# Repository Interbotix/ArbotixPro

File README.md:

# ArbotixPro
Eagle design files for Arbotix-Pro Robocontroller & source for CM730-compatible & ROS firmware versions.

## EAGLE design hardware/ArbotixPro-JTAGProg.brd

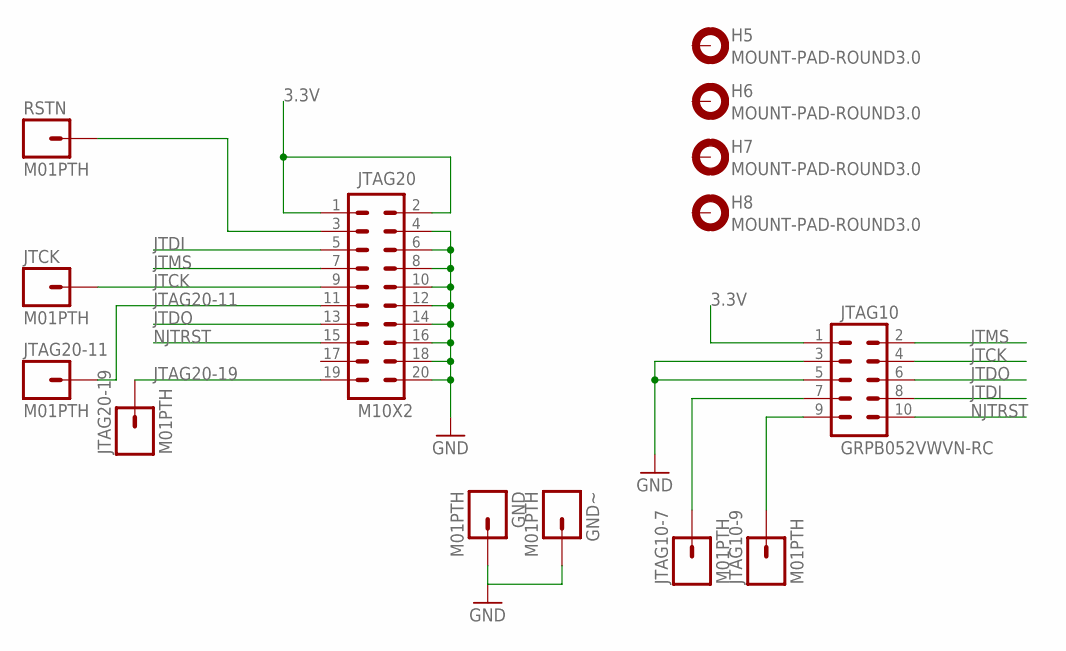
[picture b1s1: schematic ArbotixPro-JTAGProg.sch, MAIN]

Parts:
GND: M01PTH; 1X01
GND~: M01PTH; 1X01
H5, H6, H7, H8: MOUNT-PAD-ROUND3.0; 3,0-PAD
JTAG10: GRPB052VWVN-RC; 2X5_PTH_SILK_.05
JTAG10-7, JTAG10-9, JTAG20-11, JTAG20-19: M01PTH; 1X01
JTAG20: M10X2; 2X10
JTCK: M01PTH; 1X01
RSTN: M01PTH; 1X01

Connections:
3.3V: JTAG10.1, JTAG20.1, JTAG20.2
GND: GND.1, GND~.1, JTAG10.3, JTAG10.5, JTAG20.4, JTAG20.6, JTAG20.8, JTAG20.10, JTAG20.12, JTAG20.14, JTAG20.16, JTAG20.18, JTAG20.20
JTAG20-11: JTAG20.11, JTAG20-11.1
JTAG20-19: JTAG20.19, JTAG20-19.1
JTCK: JTAG10.4, JTAG20.9, JTCK.1
JTDI: JTAG10.8, JTAG20.5
JTDO: JTAG10.6, JTAG20.13
JTMS: JTAG10.2, JTAG20.7
unnamed: JTAG10.7, JTAG10-7.1
unnamed: JTAG10.9, JTAG10-9.1
NJTRST: JTAG10.10, JTAG20.15
RSTN: JTAG20.3, RSTN.1

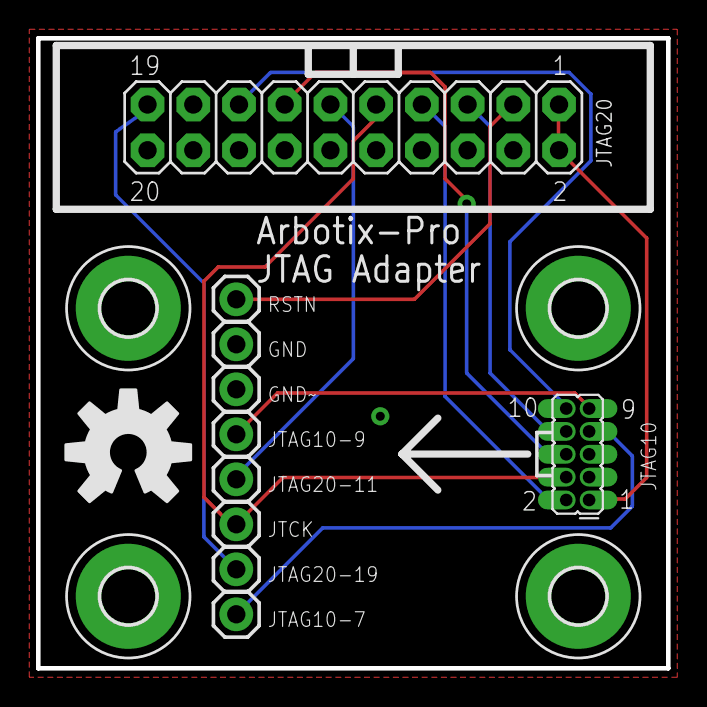
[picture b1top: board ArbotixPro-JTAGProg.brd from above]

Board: 2 copper layers, 35.0 x 35.0 mm, 15 parts (0 on the bottom side), 12 nets.

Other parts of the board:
U$1: OSHW-LOGO-L

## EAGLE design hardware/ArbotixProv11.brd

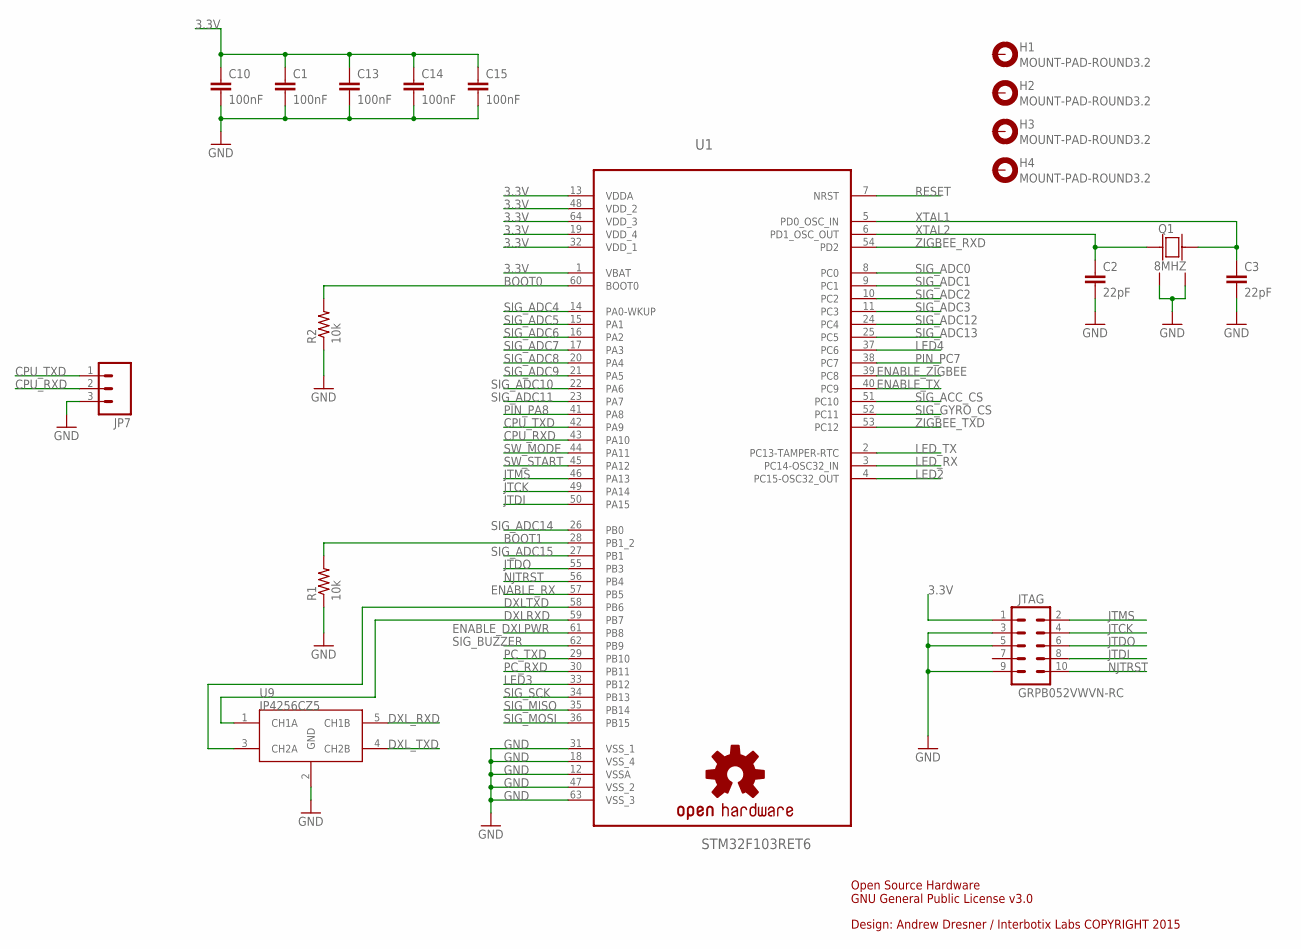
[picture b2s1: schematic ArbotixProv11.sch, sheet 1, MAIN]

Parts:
C1, C10, C13, C14, C15: 100nF; 0603-CAP
C2, C3: 22pF; 0603-CAP
H1, H2, H3, H4: MOUNT-PAD-ROUND3.2; 3,2-PAD
JP7: M03PTH; 1X03
JTAG: GRPB052VWVN-RC; 2X5_PTH_SILK_.05
LOGO1: OSHW-LOGOM; OSHW-LOGO-M
Q1: 8MHZ; 4LCC
R1, R2: 10k; 0603-RES
U1: STM32F103RET6; QFP50P1200X1200X160-64N
U9: IP4256CZ5; SOT665

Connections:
3.3V: C1.1, C10.1, C13.1, C14.1, C15.1, JTAG.1, U1.1 (VBAT), U1.13 (VDDA), U1.19 (VDD_4), U1.32 (VDD_1), U1.48 (VDD_2), U1.64 (VDD_3); also elsewhere on the board
BOOT0: R2.2, U1.60 (BOOT0)
BOOT1: R1.2, U1.28 (PB1_2)
CPU_RXD: JP7.2, U1.43 (PA10)
CPU_TXD: JP7.1, U1.42 (PA9)
DXLRXD: U1.59 (PB7), U9.1 (CH1A)
DXLTXD: U1.58 (PB6), U9.3 (CH2A)
DXL_RXD: U9.5 (CH1B); also elsewhere on the board
DXL_TXD: U9.4 (CH2B); also elsewhere on the board
ENABLE_DXLPWR: U1.61 (PB8); also elsewhere on the board
ENABLE_RX: U1.57 (PB5); also elsewhere on the board
ENABLE_TX: U1.40 (PC9); also elsewhere on the board
ENABLE_ZIGBEE: U1.39 (PC8); also elsewhere on the board
GND: C1.2, C2.2, C3.2, C10.2, C13.2, C14.2, C15.2, JP7.3, JTAG.3, JTAG.5, JTAG.9, Q1.2, Q1.4, R1.1, R2.1, U1.12 (VSSA), U1.18 (VSS_4), U1.31 (VSS_1), U1.47 (VSS_2), U1.63 (VSS_3), U9.2 (GND); also elsewhere on the board
JTCK: JTAG.4, U1.49 (PA14)
JTDI: JTAG.8, U1.50 (PA15)
JTDO: JTAG.6, U1.55 (PB3)
JTMS: JTAG.2, U1.46 (PA13)
LED2: U1.4 (PC15-OSC32_OUT); also elsewhere on the board
LED3: U1.33 (PB12); also elsewhere on the board
LED4: U1.37 (PC6); also elsewhere on the board
LED_RX: U1.3 (PC14-OSC32_IN); also elsewhere on the board
LED_TX: U1.2 (PC13-TAMPER-RTC); also elsewhere on the board
NJTRST: JTAG.10, U1.56 (PB4)
PC_RXD: U1.30 (PB11); also elsewhere on the board
PC_TXD: U1.29 (PB10); also elsewhere on the board
PIN_PA8: U1.41 (PA8); also elsewhere on the board
PIN_PC7: U1.38 (PC7)
RESET: U1.7 (NRST); also elsewhere on the board
SIG_ACC_CS: U1.51 (PC10); also elsewhere on the board
SIG_ADC0: U1.8 (PC0); also elsewhere on the board
SIG_ADC1: U1.9 (PC1); also elsewhere on the board
SIG_ADC2: U1.10 (PC2); also elsewhere on the board
SIG_ADC3: U1.11 (PC3); also elsewhere on the board
SIG_ADC4: U1.14 (PA0-WKUP); also elsewhere on the board
SIG_ADC5: U1.15 (PA1); also elsewhere on the board
SIG_ADC6: U1.16 (PA2); also elsewhere on the board
SIG_ADC7: U1.17 (PA3); also elsewhere on the board
SIG_ADC8: U1.20 (PA4); also elsewhere on the board
SIG_ADC9: U1.21 (PA5); also elsewhere on the board
SIG_ADC10: U1.22 (PA6); also elsewhere on the board
SIG_ADC11: U1.23 (PA7); also elsewhere on the board
SIG_ADC12: U1.24 (PC4); also elsewhere on the board
SIG_ADC13: U1.25 (PC5); also elsewhere on the board
SIG_ADC14: U1.26 (PB0); also elsewhere on the board
SIG_ADC15: U1.27 (PB1); also elsewhere on the board
SIG_BUZZER: U1.62 (PB9); also elsewhere on the board
SIG_GYRO_CS: U1.52 (PC11); also elsewhere on the board
SIG_MISO: U1.35 (PB14); also elsewhere on the board
SIG_MOSI: U1.36 (PB15); also elsewhere on the board
SIG_SCK: U1.34 (PB13); also elsewhere on the board
SW_MODE: U1.44 (PA11); also elsewhere on the board
SW_START: U1.45 (PA12); also elsewhere on the board
XTAL1: C3.1, Q1.3, U1.5 (PD0_OSC_IN)
XTAL2: C2.1, Q1.1, U1.6 (PD1_OSC_OUT)
ZIGBEE_RXD: U1.54 (PD2); also elsewhere on the board
ZIGBEE_TXD: U1.53 (PC12); also elsewhere on the board

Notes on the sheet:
Design: Andrew Dresner / Interbotix Labs COPYRIGHT 2015
Open Source Hardware GNU General Public License v3.0

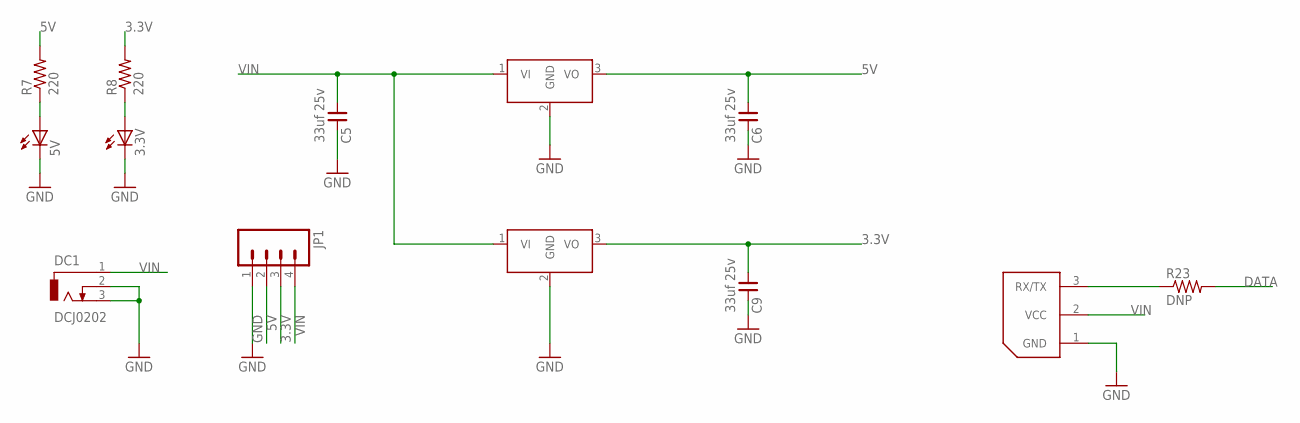
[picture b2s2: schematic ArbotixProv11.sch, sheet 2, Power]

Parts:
3.3V, 5V: LEDCHIPLED_0603; CHIPLED_0603
3V3REG: DCDC_OKI-78SR-3.3; OKI-78SRH
5VREG: DCDC_OKI-78SR-5; OKI-78SRH
C5, C6, C9: 33uf 25v; SV-C
CPU-POWER: WM18887-ND; BIOLOID
DC1: DCJ0202
JP1: M04PTH; 1X04
R7, R8: 220; 0603-RES
R23: DNP; 0603-RES

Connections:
3.3V: 3V3REG.3 (VO), C9.+ (1), JP1.3, R8.2; also elsewhere on the board
5V: 5VREG.3 (VO), C6.+ (1), JP1.2, R7.2; also elsewhere on the board
DATA: R23.2; also elsewhere on the board
GND: 3.3V.C, 3V3REG.2 (GND), 5V.C, 5VREG.2 (GND), C5.- (2), C6.- (2), C9.- (2), CPU-POWER.1 (GND), DC1.2, DC1.3, JP1.1; also elsewhere on the board
unnamed: CPU-POWER.3 (RX/TX), R23.1
unnamed: 5V.A, R7.1
unnamed: 3.3V.A, R8.1
VIN: 3V3REG.1 (VI), 5VREG.1 (VI), C5.+ (1), CPU-POWER.2 (VCC), DC1.1, JP1.4; also elsewhere on the board

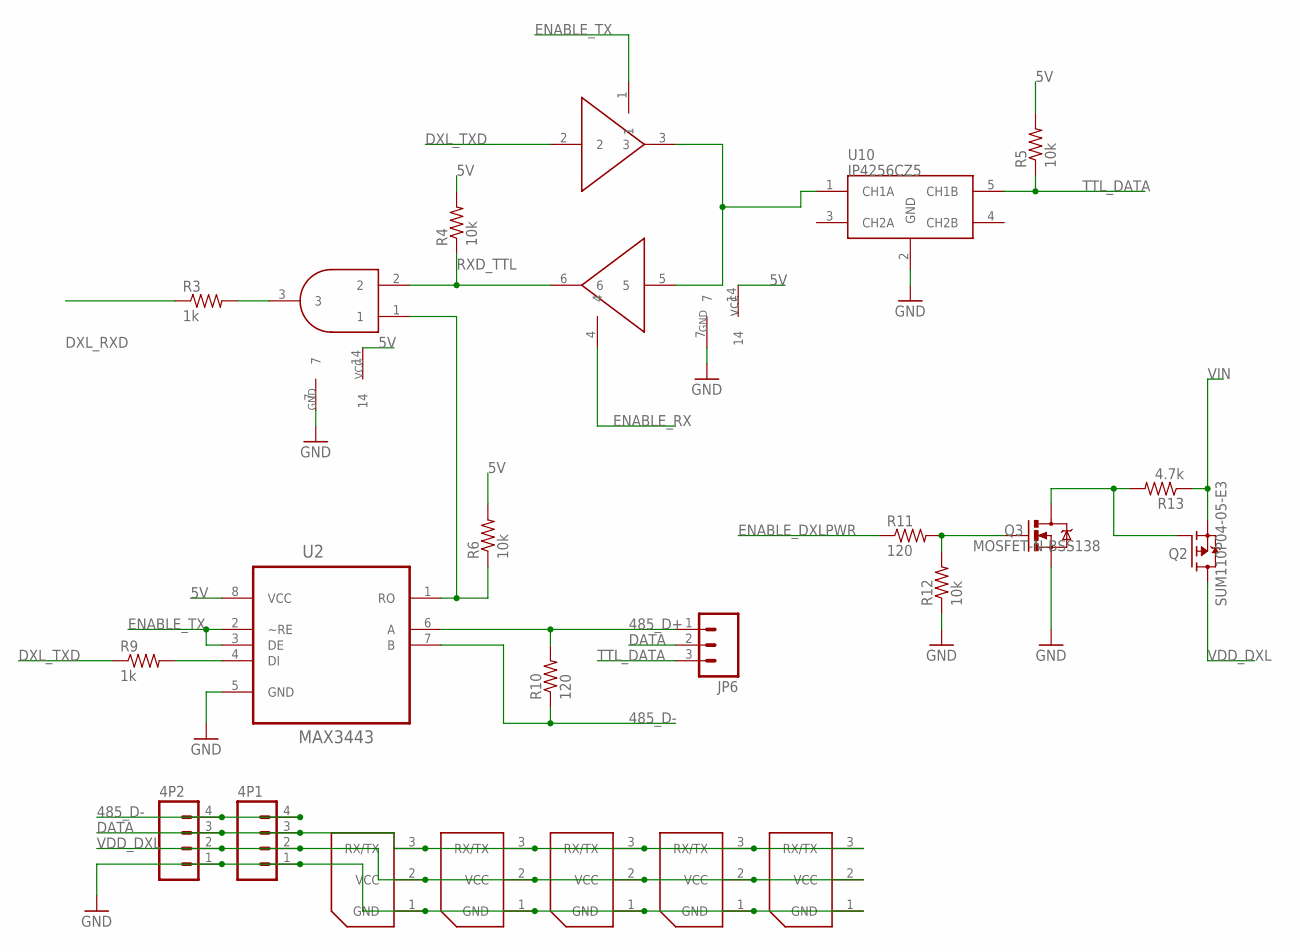
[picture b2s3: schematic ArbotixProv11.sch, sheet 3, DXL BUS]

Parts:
3P1, 3P2, 3P3, 3P4, 3P5: WM18887-ND; BIOLOID
4P1, 4P2: M04PTH; 1X04
JP6: M03PTH; 1X03
Q2: SUM110P04-05-E3; TO263
Q3: MOSFET-N-BSS138; SOT23
R3, R9: 1k; 0603-RES
R4, R5, R6, R12: 10k; 0603-RES
R10, R11: 120; 0603-RES
R13: 4.7k; 0603-RES
U2: MAX3443; SOIC127P600X175-8N
U6: 74HC08D,653; 14-SOIC
U7: 74HC126D,653; 14-SOIC
U10: IP4256CZ5; SOT665

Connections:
5V: R4.2, R5.2, R6.2, U2.8 (VCC), U6.14, U7.14; also elsewhere on the board
485_D+: JP6.1, R10.2, U2.6 (A)
485_D-: 4P1.4, 4P2.4, R10.1, U2.7 (B)
DATA: 3P1.3 (RX/TX), 3P2.3 (RX/TX), 3P3.3 (RX/TX), 3P4.3 (RX/TX), 3P5.3 (RX/TX), 4P1.3, 4P2.3, JP6.2; also elsewhere on the board
DXL_RXD: R3.1; also elsewhere on the board
DXL_TXD: R9.1, U7.2; also elsewhere on the board
ENABLE_DXLPWR: R11.1; also elsewhere on the board
ENABLE_RX: U7.4; also elsewhere on the board
ENABLE_TX: U2.2 (~RE), U2.3 (DE), U7.1; also elsewhere on the board
GND: 3P1.1 (GND), 3P2.1 (GND), 3P3.1 (GND), 3P4.1 (GND), 3P5.1 (GND), 4P1.1, 4P2.1, Q3.2 (S), R12.1, U2.5 (GND), U6.7, U7.7, U10.2 (GND); also elsewhere on the board
unnamed: Q3.1 (G), R11.2, R12.2
unnamed: R3.2, U6.3
unnamed: R9.2, U2.4 (DI)
unnamed: R6.1, U2.1 (RO), U6.1
unnamed: Q2.1 (G), Q3.3 (D), R13.2
unnamed: U7.3, U7.5, U10.1 (CH1A)
RXD_TTL: R4.1, U6.2, U7.6
TTL_DATA: JP6.3, R5.1, U10.5 (CH1B)
VDD_DXL: 3P1.2 (VCC), 3P2.2 (VCC), 3P3.2 (VCC), 3P4.2 (VCC), 3P5.2 (VCC), 4P1.2, 4P2.2, Q2.3 (D)
VIN: Q2.2 (S), R13.1; also elsewhere on the board

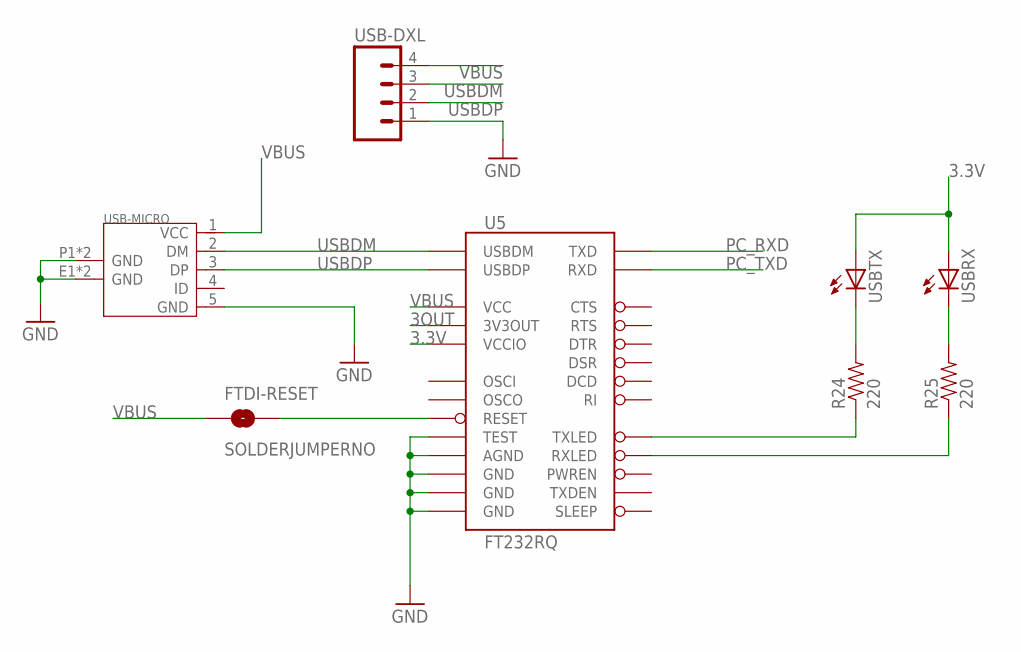
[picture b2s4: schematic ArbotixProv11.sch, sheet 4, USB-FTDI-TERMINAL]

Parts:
FTDI-RESET: SOLDERJUMPERNO; SJ_2S-NO
R24, R25: 220; 0603-RES
U5: FT232RQ; QFN-32
USB-DXL: M04PTH; 1X04
USB-MICRO: MICRO-USB-5P-340015001; B-SMD-5P
USBRX: LEDCHIPLED_0603; CHIPLED_0603
USBTX: LEDCHIPLED_0603; CHIPLED_0603

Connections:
3.3V: U5.1 (VCCIO), USBRX.A, USBTX.A; also elsewhere on the board
3OUT: U5.16 (3V3OUT)
GND: U5.4 (GND), U5.17 (GND), U5.20 (GND), U5.24 (AGND), U5.26 (TEST), USB-DXL.1, USB-MICRO.5 (GND), USB-MICRO.E1 (GND), USB-MICRO.E2 (GND), USB-MICRO.P1 (GND), USB-MICRO.P2 (GND); also elsewhere on the board
unnamed: FTDI-RESET.2, U5.18 (RESET)
unnamed: R24.2, USBTX.C
unnamed: R25.2, USBRX.C
unnamed: R24.1, U5.22 (TXLED)
unnamed: R25.1, U5.21 (RXLED)
PC_RXD: U5.30 (TXD); also elsewhere on the board
PC_TXD: U5.2 (RXD); also elsewhere on the board
USBDM: U5.15 (USBDM), USB-DXL.3, USB-MICRO.2 (DM)
USBDP: U5.14 (USBDP), USB-DXL.2, USB-MICRO.3 (DP)
VBUS: FTDI-RESET.1, U5.19 (VCC), USB-DXL.4, USB-MICRO.1 (VCC)

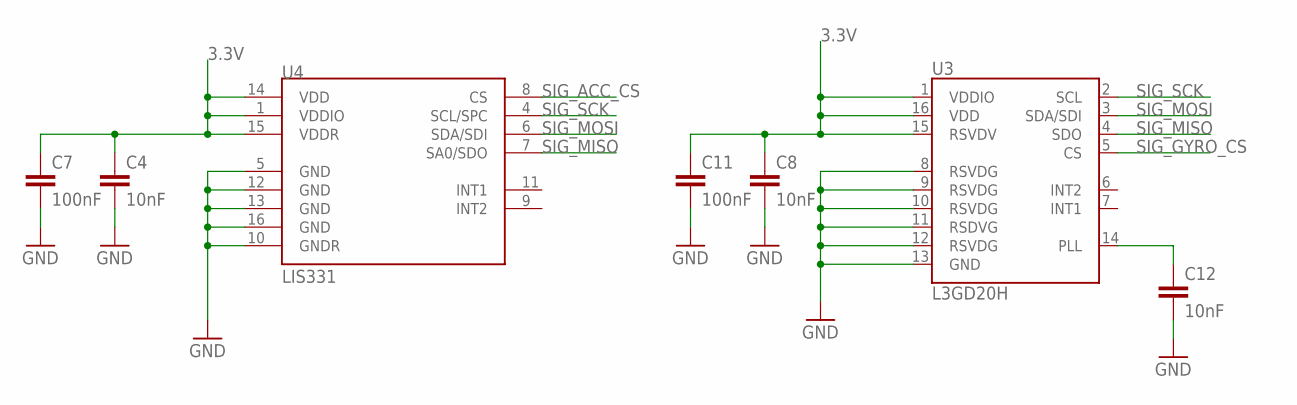
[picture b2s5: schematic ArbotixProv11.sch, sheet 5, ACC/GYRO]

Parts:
C4, C8, C12: 10nF; 0603-CAP
C7, C11: 100nF; 0603-CAP
U3: L3GD20H; LGA16-3MM
U4: LIS331; LGA16-3MM

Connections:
3.3V: C4.1, C7.1, C8.1, C11.1, U3.1 (VDDIO), U3.15 (RSVDV), U3.16 (VDD), U4.1 (VDDIO), U4.14 (VDD), U4.15 (VDDR); also elsewhere on the board
GND: C4.2, C7.2, C8.2, C11.2, C12.2, U3.8 (RSVDG), U3.9 (RSVDG), U3.10 (RSVDG), U3.11 (RSDVG), U3.12 (RSVDG), U3.13 (GND), U4.5 (GND), U4.10 (GNDR), U4.12 (GND), U4.13 (GND), U4.16 (GND); also elsewhere on the board
unnamed: C12.1, U3.14 (PLL)
SIG_ACC_CS: U4.8 (CS); also elsewhere on the board
SIG_GYRO_CS: U3.5 (CS); also elsewhere on the board
SIG_MISO: U3.4 (SDO), U4.7 (SA0/SDO); also elsewhere on the board
SIG_MOSI: U3.3 (SDA/SDI), U4.6 (SDA/SDI); also elsewhere on the board
SIG_SCK: U3.2 (SCL), U4.4 (SCL/SPC); also elsewhere on the board

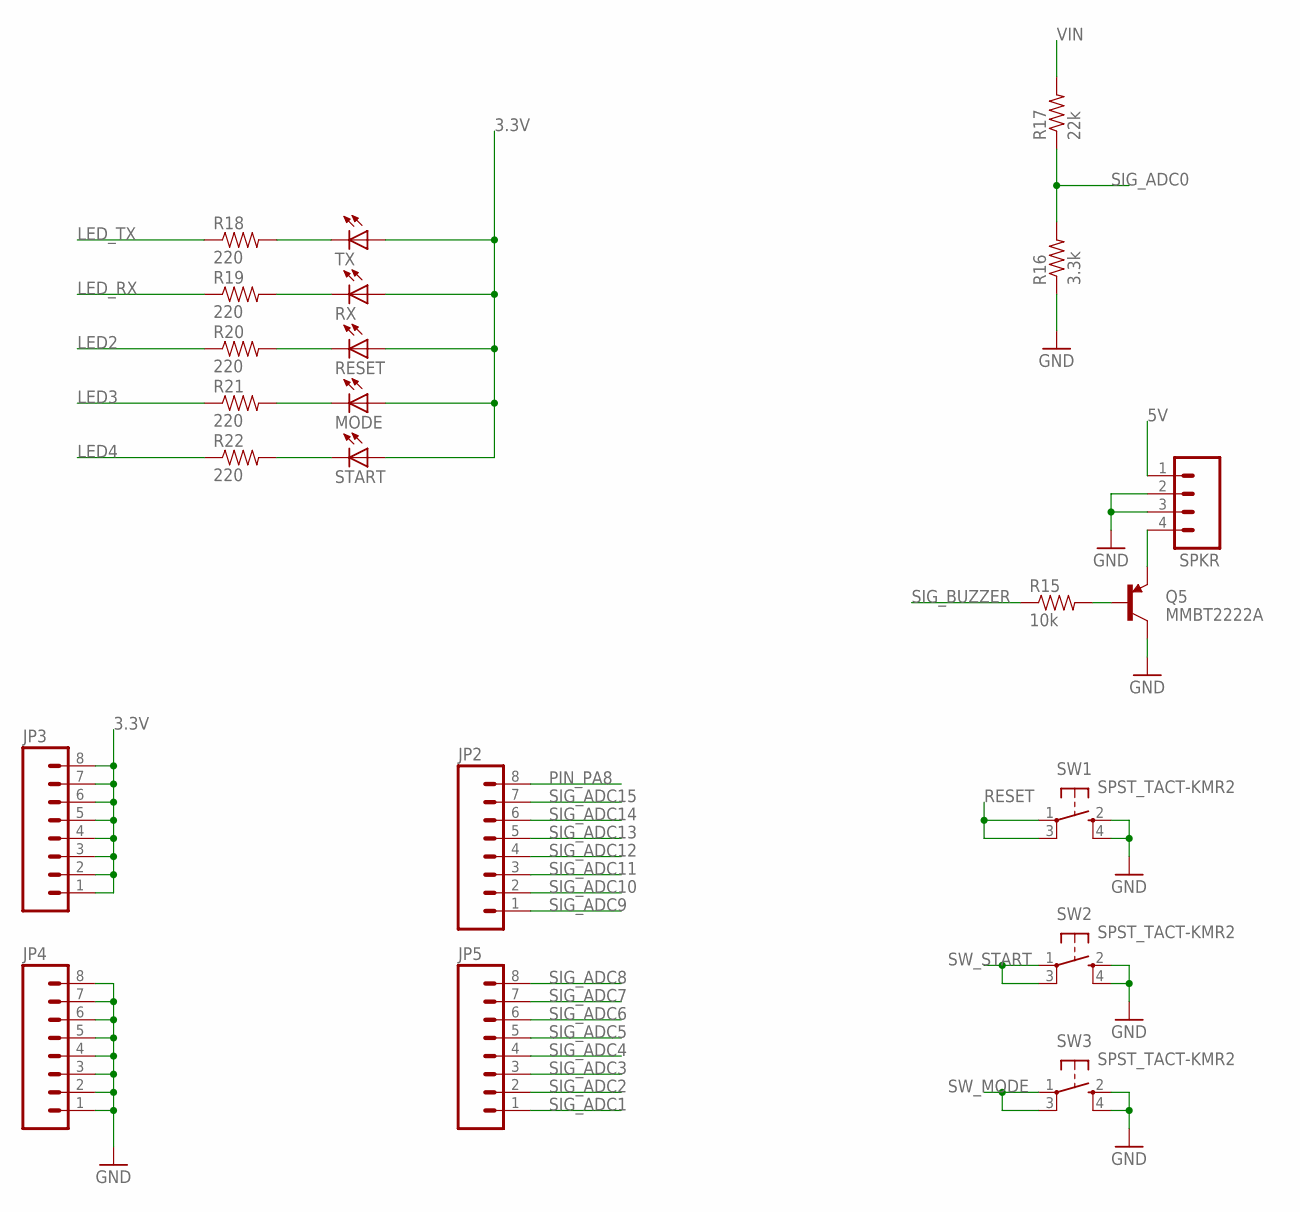
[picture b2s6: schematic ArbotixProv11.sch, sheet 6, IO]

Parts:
JP2, JP3, JP4, JP5: M08SILK_FEMALE_PTH; 1X08
MODE: LEDCHIP-LED0603; CHIP-LED0603
Q5: MMBT2222A; SOT23
R15: 10k; 0603-RES
R16: 3.3k; 0603-RES
R17: 22k; 0603-RES
R18, R19, R20, R21, R22: 220; 0603-RES
RESET: LEDCHIP-LED0603; CHIP-LED0603
RX: LEDCHIP-LED0603; CHIP-LED0603
SPKR: M04PTH; 1X04
START: LEDCHIP-LED0603; CHIP-LED0603
SW1, SW2, SW3: SPST_TACT-KMR2; KMR2
TX: LEDCHIP-LED0603; CHIP-LED0603

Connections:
3.3V: JP3.1, JP3.2, JP3.3, JP3.4, JP3.5, JP3.6, JP3.7, JP3.8, MODE.A, RESET.A, RX.A, START.A, TX.A; also elsewhere on the board
5V: SPKR.1; also elsewhere on the board
GND: JP4.1, JP4.2, JP4.3, JP4.4, JP4.5, JP4.6, JP4.7, JP4.8, Q5.3 (C), R16.1, SPKR.2, SPKR.3, SW1.2 (S), SW1.4 (S1), SW2.2 (S), SW2.4 (S1), SW3.2 (S), SW3.4 (S1); also elsewhere on the board
LED2: R20.1; also elsewhere on the board
LED3: R21.1; also elsewhere on the board
LED4: R22.1; also elsewhere on the board
LED_RX: R19.1; also elsewhere on the board
LED_TX: R18.1; also elsewhere on the board
unnamed: R18.2, TX.C
unnamed: R19.2, RX.C
unnamed: Q5.1 (B), R15.2
unnamed: Q5.2 (E), SPKR.4
unnamed: R20.2, RESET.C
unnamed: MODE.C, R21.2
unnamed: R22.2, START.C
PIN_PA8: JP2.8; also elsewhere on the board
RESET: SW1.1, SW1.3 (P1); also elsewhere on the board
SIG_ADC0: R16.2, R17.1; also elsewhere on the board
SIG_ADC1: JP5.1; also elsewhere on the board
SIG_ADC2: JP5.2; also elsewhere on the board
SIG_ADC3: JP5.3; also elsewhere on the board
SIG_ADC4: JP5.4; also elsewhere on the board
SIG_ADC5: JP5.5; also elsewhere on the board
SIG_ADC6: JP5.6; also elsewhere on the board
SIG_ADC7: JP5.7; also elsewhere on the board
SIG_ADC8: JP5.8; also elsewhere on the board
SIG_ADC9: JP2.1; also elsewhere on the board
SIG_ADC10: JP2.2; also elsewhere on the board
SIG_ADC11: JP2.3; also elsewhere on the board
SIG_ADC12: JP2.4; also elsewhere on the board
SIG_ADC13: JP2.5; also elsewhere on the board
SIG_ADC14: JP2.6; also elsewhere on the board
SIG_ADC15: JP2.7; also elsewhere on the board
SIG_BUZZER: R15.1; also elsewhere on the board
SW_MODE: SW3.1, SW3.3 (P1); also elsewhere on the board
SW_START: SW2.1, SW2.3 (P1); also elsewhere on the board
VIN: R17.2; also elsewhere on the board

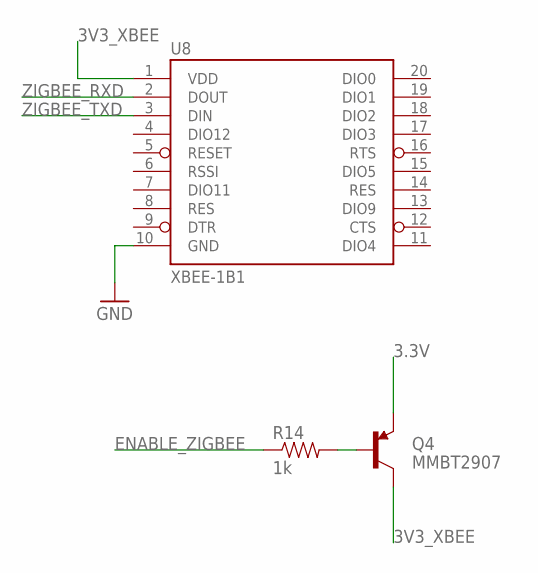
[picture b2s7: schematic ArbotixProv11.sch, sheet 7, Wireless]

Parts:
Q4: MMBT2907; SOT23
R14: 1k; 0603-RES
U8: XBEE-1B1; XBEE-1

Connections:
3.3V: Q4.2 (E); also elsewhere on the board
3V3_XBEE: Q4.3 (C), U8.1 (VDD)
ENABLE_ZIGBEE: R14.1; also elsewhere on the board
GND: U8.10 (GND); also elsewhere on the board
unnamed: Q4.1 (B), R14.2
ZIGBEE_RXD: U8.2 (DOUT); also elsewhere on the board
ZIGBEE_TXD: U8.3 (DIN); also elsewhere on the board

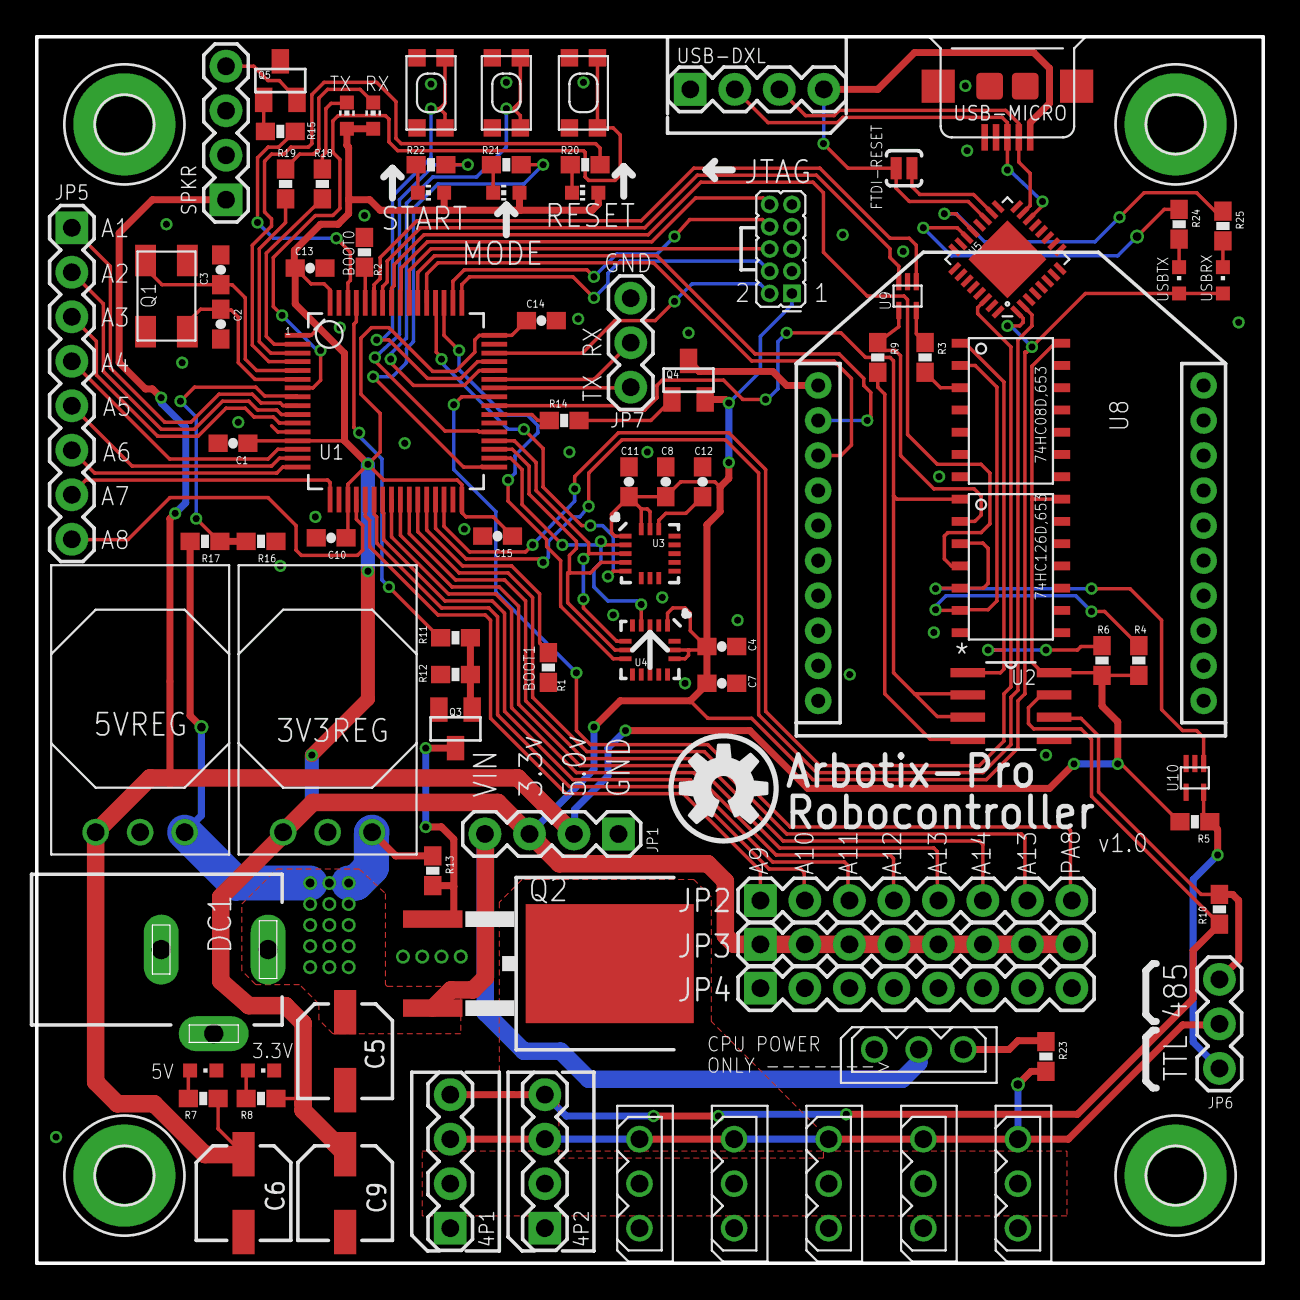
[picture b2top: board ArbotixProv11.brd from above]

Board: 2 copper layers, 70.0 x 70.0 mm, 95 parts (0 on the bottom side), 91 nets.

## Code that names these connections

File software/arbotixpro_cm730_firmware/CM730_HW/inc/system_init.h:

/************************* (C) COPYRIGHT 2010 ROBOTIS *************************
* File Name          : system_init.h
* Author             : zerom
* Version            : V0.1
* Date               : 2010/08/25
* Description        : This file contains the defines used for Sys init fuctions
*******************************************************************************/

/* Define to prevent recursive inclusion -------------------------------------*/
#ifndef __SYSTEM_INIT_H
#define __SYSTEM_INIT_H

/* Includes ------------------------------------------------------------------*/
/* Exported types ------------------------------------------------------------*/
/* Exported constants --------------------------------------------------------*/



///////////////////PORTA//////////////////////////////////////////////////////////
#define PIN_ADC4				GPIO_Pin_0
#define PIN_ADC5				GPIO_Pin_1
#define PIN_ADC6				GPIO_Pin_2
#define PIN_ADC7				GPIO_Pin_3
#define PIN_ADC8				GPIO_Pin_4
#define PIN_ADC9				GPIO_Pin_5
#define PIN_ADC10				GPIO_Pin_6
#define PIN_ADC11				GPIO_Pin_7

//#define PIN_LED6_R				GPIO_Pin_8
#define PIN_PA8					GPIO_Pin_8

#define PIN_CPU_TXD				GPIO_Pin_9
#define PIN_CPU_RXD				GPIO_Pin_10

//#define PIN_LED6_G				GPIO_Pin_11
#define PIN_SW_MODE				GPIO_Pin_11

//#define PIN_LED6_B				GPIO_Pin_12
#define PIN_SW_START			GPIO_Pin_12

#define PIN_PA13				GPIO_Pin_13

//#define PIN_SW_START			GPIO_Pin_14
#define PIN_PA15				GPIO_Pin_14

//#define PIN_SW_MODE				GPIO_Pin_15
#define PIN_PA14				GPIO_Pin_15

#define PORT_ADC4				GPIOA
#define PORT_ADC5				GPIOA
#define PORT_ADC6				GPIOA
#define PORT_ADC7				GPIOA
#define PORT_ADC8				GPIOA
#define PORT_ADC9				GPIOA
#define PORT_ADC10				GPIOA
#define PORT_ADC11				GPIOA

//#define PORT_LED6_R				GPIOA
#define PORT_PA8				GPIOA

#define PORT_CPU_TXD			GPIOA1
#define PORT_CPU_RXD			GPIOA

//#define PORT_LED6_G				GPIOA
//#define PORT_LED6_B				GPIOA
#define PORT_SW_MODE			GPIOA
#define PORT_SW_START			GPIOA

#define PORT_PA13				GPIOA

#define PORT_PA14				GPIOA
#define PORT_PA15				GPIOA


///////////////////PORTB//////////////////////////////////////////////////////////
#define PIN_ADC14				GPIO_Pin_0
#define PIN_ADC15				GPIO_Pin_1
#define PIN_BOOT1				GPIO_Pin_2


//#define PIN_ENABLE_ZIGBEE		GPIO_Pin_3
#define PIN_PB3					GPIO_Pin_3

//#define PIN_ENABLE_TXD			GPIO_Pin_4
#define PIN_PB4					GPIO_Pin_4

#define PIN_ENABLE_RXD			GPIO_Pin_5
#define PIN_DXL_TXD				GPIO_Pin_6
#define PIN_DXL_RXD				GPIO_Pin_7
#define PIN_ENABLE_DXLPWR		GPIO_Pin_8
#define PIN_BUZZER				GPIO_Pin_9
#define PIN_PC_TXD				GPIO_Pin_10
#define PIN_PC_RXD				GPIO_Pin_11
#define PIN_LED3				GPIO_Pin_12
#define PIN_SIG_SCK				GPIO_Pin_13
#define PIN_SIG_MISO			GPIO_Pin_14
#define PIN_SIG_MOSI			GPIO_Pin_15

#define PORT_ADC14				GPIOB
#define PORT_ADC15				GPIOB
#define PORT_BOOT1				GPIOB

//#define PORT_ENABLE_ZIGBEE	GPIOB
#define PORT_PB3				GPIOB

//#define PORT_ENABLE_TXD			GPIOB
#define PORT_PB4				GPIOB

#define PORT_ENABLE_RXD			GPIOB
#define PORT_DXL_TXD			GPIOB
#define PORT_DXL_RXD			GPIOB
#define PORT_ENABLE_DXLPWR		GPIOB
#define PORT_BUZZER				GPIOB
#define PORT_PC_TXD				GPIOB
#define PORT_PC_RXD				GPIOB
#define PORT_LED3				GPIOB
#define PORT_SIG_SCK			GPIOB
#define PORT_SIG_MISO			GPIOB
#define PORT_SIG_MOSI			GPIOB



///////////////////PORTC//////////////////////////////////////////////////////////
#define PIN_ADC0				GPIO_Pin_0
#define PIN_ADC1				GPIO_Pin_1
#define PIN_ADC2				GPIO_Pin_2
#define PIN_ADC3				GPIO_Pin_3
#define PIN_ADC12				GPIO_Pin_4
#define PIN_ADC13				GPIO_Pin_5
#define PIN_LED4				GPIO_Pin_6


//#define PIN_LED5_R				GPIO_Pin_7
#define PIN_PC7					GPIO_Pin_7

//#define PIN_LED5_G				GPIO_Pin_8
#define PIN_ENABLE_ZIGBEE		GPIO_Pin_8

//#define PIN_LED5_B				GPIO_Pin_9
#define PIN_ENABLE_TXD			GPIO_Pin_9

#define PIN_SIG_ACC_CS			GPIO_Pin_10
#define PIN_SIG_GYRO_CS			GPIO_Pin_11
#define PIN_ZIGBEE_TXD			GPIO_Pin_12
#define PIN_LED_TX				GPIO_Pin_13
#define PIN_LED_RX				GPIO_Pin_14
#define PIN_LED2				GPIO_Pin_15


#define PORT_ADC0				GPIOC
#define PORT_ADC1				GPIOC
#define PORT_ADC2				GPIOC
#define PORT_ADC3				GPIOC
#define PORT_ADC12				GPIOC
#define PORT_ADC13				GPIOC
#define PORT_LED4				GPIOC

//#define PORT_LED5_R				GPIOC
#define PORT_PC7				GPIOC

//#define PORT_LED5_G				GPIOC
#define PORT_ENABLE_ZIGBEE		GPIOC

//#define PORT_LED5_B				GPIOC
#define PORT_ENABLE_TXD			GPIOC

#define PORT_SIG_ACC_CS			GPIOC
#define PORT_SIG_GYRO_CS		GPIOC
#define PORT_ZIGBEE_TXD			GPIOC
#define PORT_LED_TX				GPIOC
#define PORT_LED_RX				GPIOC
#define PORT_LED2				GPIOC



///////////////////PORTD///////////////////////////////////////////////////////
#define PIN_ZIGBEE_RXD			GPIO_Pin_2
#define PORT_ZIGBEE_RXD			GPIOD


/////////////////////////// LED REDEFINE /////////////////////////////////////////
#define PIN_LED_MANAGE		PIN_LED2
#define PIN_LED_EDIT		PIN_LED3
#define PIN_LED_PLAY		PIN_LED4

#define PORT_LED_MANAGE		PORT_LED2
#define PORT_LED_EDIT		PORT_LED3
#define PORT_LED_PLAY		PORT_LED4

//#define PIN_LED_POWER		PIN_LED6_R

//#define PIN_LED_AUX			PIN_LED5_R
//#define PIN_LED_AUX			PIN_PC7

/*


/* Exported macro ------------------------------------------------------------*/
/* Exported functions ------------------------------------------------------- */

void RCC_Configuration(void);
void GPIO_Configuration(void);
void NVIC_Configuration(void);
void USART_Configuration(u8 PORT, u32 baudrate);
u32 USART_GetBaudrate(u8 PORT);
void ADC_Configuration(void);
void Timer_Configuration(void);
void SysTick_Configuration(void);
void EXTI_Configuration(void);
void System_Configuration(void);

void SPI_Configuration(void);
void Buzzer_Configuration(void);



#endif /* __SYSTEM_INIT_H */

/************************ (C) COPYRIGHT 2010 ROBOTIS ********END OF FILE*******/

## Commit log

2015-04-29 added eaglecad files, restructure folders
2015-04-29 Added pin mappings xls
2015-05-06 Added PDF Schematic
    Thanks Kurt!
2016-01-07 Addition of compiled output files.
    new file: CM730.bin
    new file: CM730.elf
    new file: CM730.elf.map
    new file: CM730.hex
    new file: CM730.lss

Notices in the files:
parts and their libraries:
SparkFun-Connectors2: Licensing: Creative Commons ShareAlike 4.0 International - https://creativecommons.org/licenses/by-sa/4.0
